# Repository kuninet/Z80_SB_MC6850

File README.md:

# Z80_SB_MC6850

## 概要
- Z80 CPUを搭載した シングルボードコンピューターです。シリアルチップは MC6850です。
  - 以下のGrrant氏の回路図を参考に、SBC8080バスへ接続できるように改良したものとなります。
  - http://searle.hostei.com/grant/z80/SimpleZ80_32K.html

## 回路図

## 部品表
- 部品表は以下にあります。
  - [https://github.com/kuninet/Z80_SB_MC6850/blob/master/KiCAD/Z80-GRANT.ods](https://github.com/kuninet/Z80_SB_MC6850/blob/master/KiCAD/Z80-GRANT.ods)

## 注意点
- ★本基板は試作して確認中のため不具合を含んでいる可能性があります。

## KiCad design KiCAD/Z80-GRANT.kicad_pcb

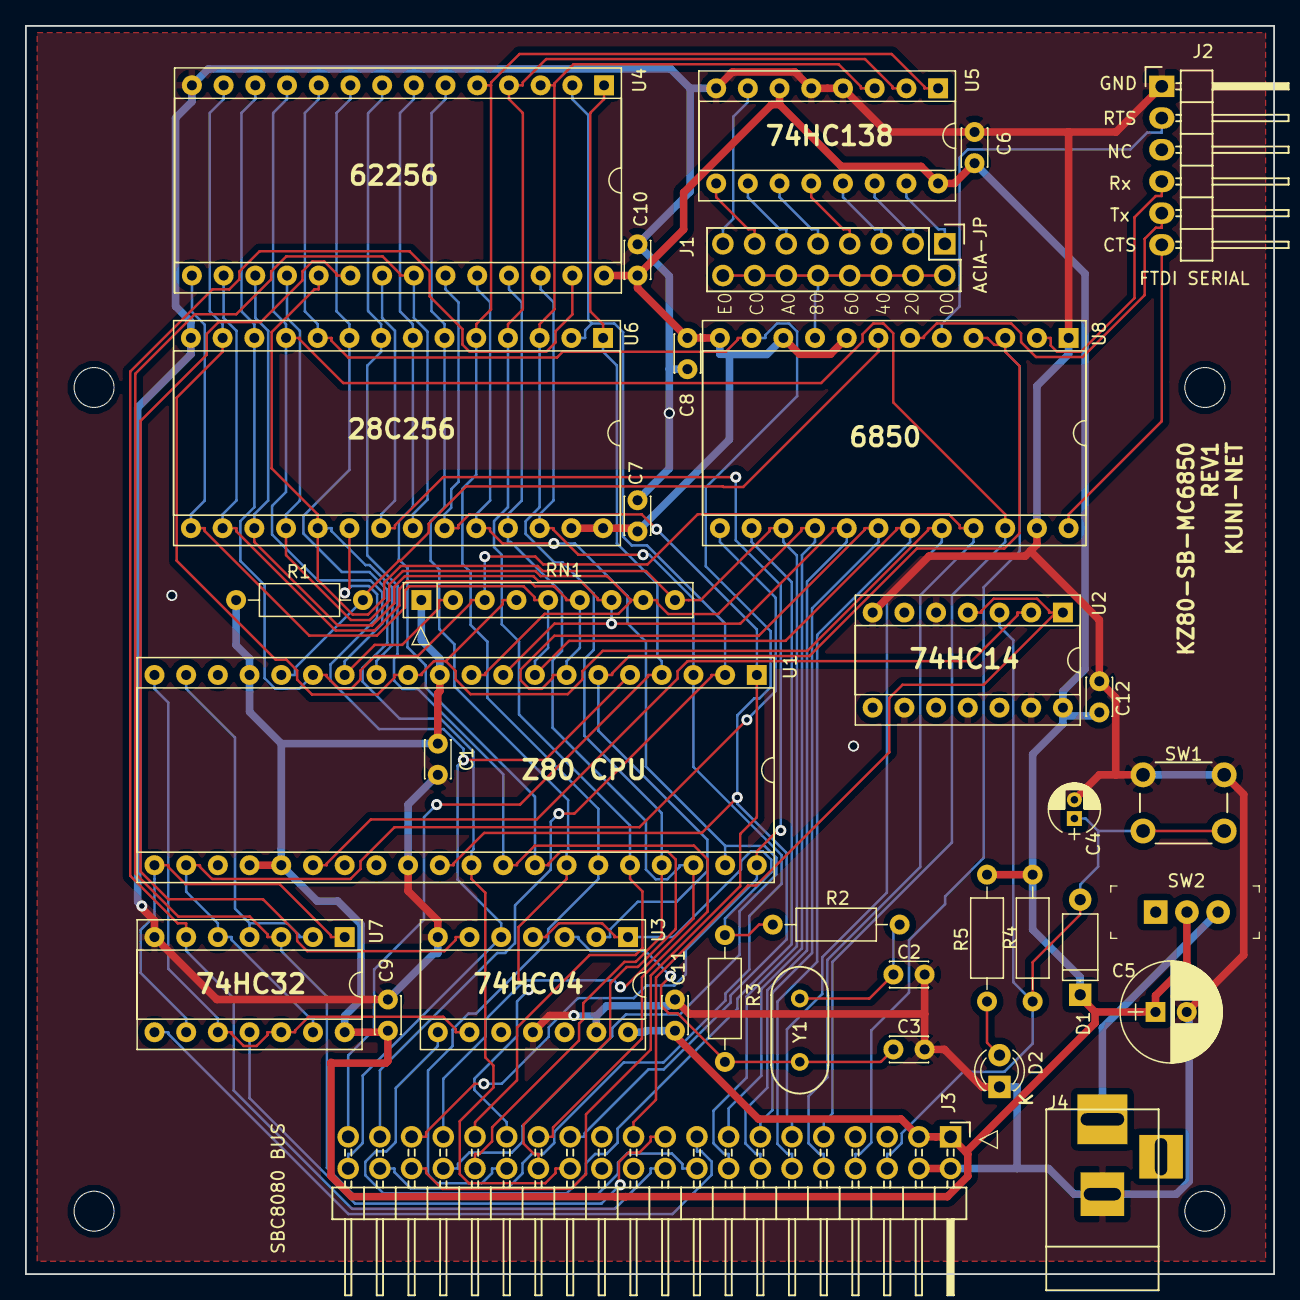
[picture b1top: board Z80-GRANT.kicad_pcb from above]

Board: 2 copper layers, 100.0 x 100.0 mm, 39 parts (0 on the bottom side), 59 nets.

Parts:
C1, C6, C7, C8, C9, C10, C11, C12: 0.1u; C_Disc_D3.0mm_W2.0mm_P2.50mm
C2, C3: 22p; C_Disc_D3.0mm_W2.0mm_P2.50mm
C4: 47u; CP_Radial_D4.0mm_P1.50mm
C5: 100u; CP_Radial_D8.0mm_P2.50mm
D1: D; D_A-405_P7.62mm_Horizontal
D2: LED; LED_D3.0mm
J1: ACIA-J; Pin_Header_Straight_2x08
J2: Conn_01x06; Pin_Header_Angled_1x06
J3: SBC8080 BUS; Pin_Header_Angled_2x20
J4: Jack-DC; BARREL_JACK
M1, M2, M3, M4: MountingHole_M3; MountingHole_3.2mm_M3
R1: 3.3k; R_Axial_DIN0207_L6.3mm_D2.5mm_P10.16mm_Horizontal
R2, R5: 1k; R_Axial_DIN0207_L6.3mm_D2.5mm_P10.16mm_Horizontal
R3: 1M; R_Axial_DIN0207_L6.3mm_D2.5mm_P10.16mm_Horizontal
R4: 2.2k; R_Axial_DIN0207_L6.3mm_D2.5mm_P10.16mm_Horizontal
RN1: R_Network08; R_Array_SIP9
SW1: SW_Push; SW_PUSH_6mm
SW2: SW_SPDT; Switch_Slide_11.6x4mm_EG1218
U1: Z80CPU; DIP-40_W15.24mm_Socket
U2: 74HC14; DIP-14_W7.62mm_Socket
U3: 74HC04; DIP-14_W7.62mm_Socket
U4: 62256; DIP-28_W15.24mm_Socket
U5: 74LS138; DIP-16_W7.62mm_Socket
U6: 28C256; DIP-28_W15.24mm_Socket
U7: 74LS32; DIP-14_W7.62mm_Socket
U8: 6850; DIP-24_W15.24mm_Socket
Y1: Crystal; HC-49V

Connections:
A0: J3.25, U1.30, U4.10, U6.10, U8.11
A1: J3.26, U1.31, U4.9, U6.9
A2: J3.27, U1.32, U4.8, U6.8
A3: J3.28, U1.33, U4.7, U6.7
A4: J3.29, U1.34, U4.6, U6.6
A5: J3.30, U1.35, U4.5, U5.1, U6.5
A6: J3.31, U1.36, U4.4, U5.2, U6.4
A7: J3.32, U1.37, U4.3, U5.3, U6.3
A8: J3.33, U1.38, U4.25, U6.25
A9: J3.34, U1.39, U4.24, U6.24
A10: J3.35, U1.40, U4.21, U6.21
A11: J3.36, U1.1, U4.23, U6.23
A12: J3.37, U1.2, U4.2, U6.2
A13: J3.38, U1.3, U4.26, U6.26
A14: J3.39, U1.4, U4.1, U6.1
A15: J3.40, U1.5, U3.5, U6.20
CLK: J3.8, U1.6, U3.2, U8.3, U8.4
D0: J3.9, RN1.2, U1.14, U4.11, U6.11, U8.22
D1: J3.10, RN1.3, U1.15, U4.12, U6.12, U8.21
D2: J3.11, RN1.4, U1.12, U4.13, U6.13, U8.20
D3: J3.12, RN1.5, U1.8, U4.15, U6.15, U8.19
D4: J3.13, RN1.6, U1.7, U4.16, U6.16, U8.18
D5: J3.14, RN1.7, U1.9, U4.17, U6.17, U8.17
D6: J3.15, RN1.8, U1.10, U4.18, U6.18, U8.16
D7: J3.16, RN1.9, U1.13, U4.19, U6.19, U8.15
GND: C1.2, C2.2, C3.2, C4.2, C5.2, C6.2, C7.2, C8.2, C9.2, C10.2, C11.2, C12.2, D2.1, J2.1, J3.2, J3.4, J4.2, SW1.1, U1.29, U2.5, U2.7, U2.9, U2.11, U2.13, U3.7, U3.11, U3.13, U4.14, U5.4, U5.5, U5.8, U6.14, U7.7, U8.1, U8.23
unnamed: C2.1, R2.1, Y1.1
unnamed: C3.1, R3.1, U3.3, Y1.2
unnamed: D2.2, R5.1
unnamed: J1.1, U5.15
unnamed: J1.3, U5.14
unnamed: J1.5, U5.13
unnamed: J1.7, U5.12
unnamed: J1.9, U5.11
unnamed: J1.2, J1.4, J1.6, J1.8, J1.10, J1.12, J1.14, J1.16, U8.9
unnamed: J1.11, U5.10
unnamed: J1.13, U5.9
unnamed: J1.15, U5.7
unnamed: J2.2, U8.5
unnamed: J2.4, U8.2
unnamed: J2.5, U8.6
unnamed: J2.6, U8.24
unnamed: J4.1, SW2.3
unnamed: R2.2, R3.2, U3.1, U3.4
unnamed: U1.26, U2.2
unnamed: U3.6, U4.20
unnamed: U3.8, U8.14
RES: J3.21, U2.1, U2.4
VCC: C1.1, C5.1, C6.1, C7.1, C8.1, C9.1, C10.1, C11.1, C12.1, D1.1, J3.1, J3.3, R1.2, R4.2, R5.2, RN1.1, SW2.2, U1.11, U1.17, U1.24, U1.25, U2.14, U3.14, U4.28, U5.6, U5.16, U6.27, U6.28, U7.14, U8.8, U8.10, U8.12
~INT: R1.1, U1.16, U8.7
~IORD: J3.17, U7.8
~IOREQ: U1.20, U3.9, U7.10, U7.12
~IOWR: J3.19, U7.11
~MEMRD: J3.18, U4.22, U6.22, U7.3
~MEMWR: J3.20, U4.27, U7.6
~MREQ: U1.19, U7.2, U7.4
~RD: U1.21, U7.1, U7.9
~RESIN: C4.1, D1.2, J3.6, R4.1, SW1.2, U2.3
~WR: U1.22, U7.5, U7.13, U8.13

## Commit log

2018-12-28 init commit
2018-12-28 Create LICENSE
2018-12-28 回路図イメージ、部品表追加
